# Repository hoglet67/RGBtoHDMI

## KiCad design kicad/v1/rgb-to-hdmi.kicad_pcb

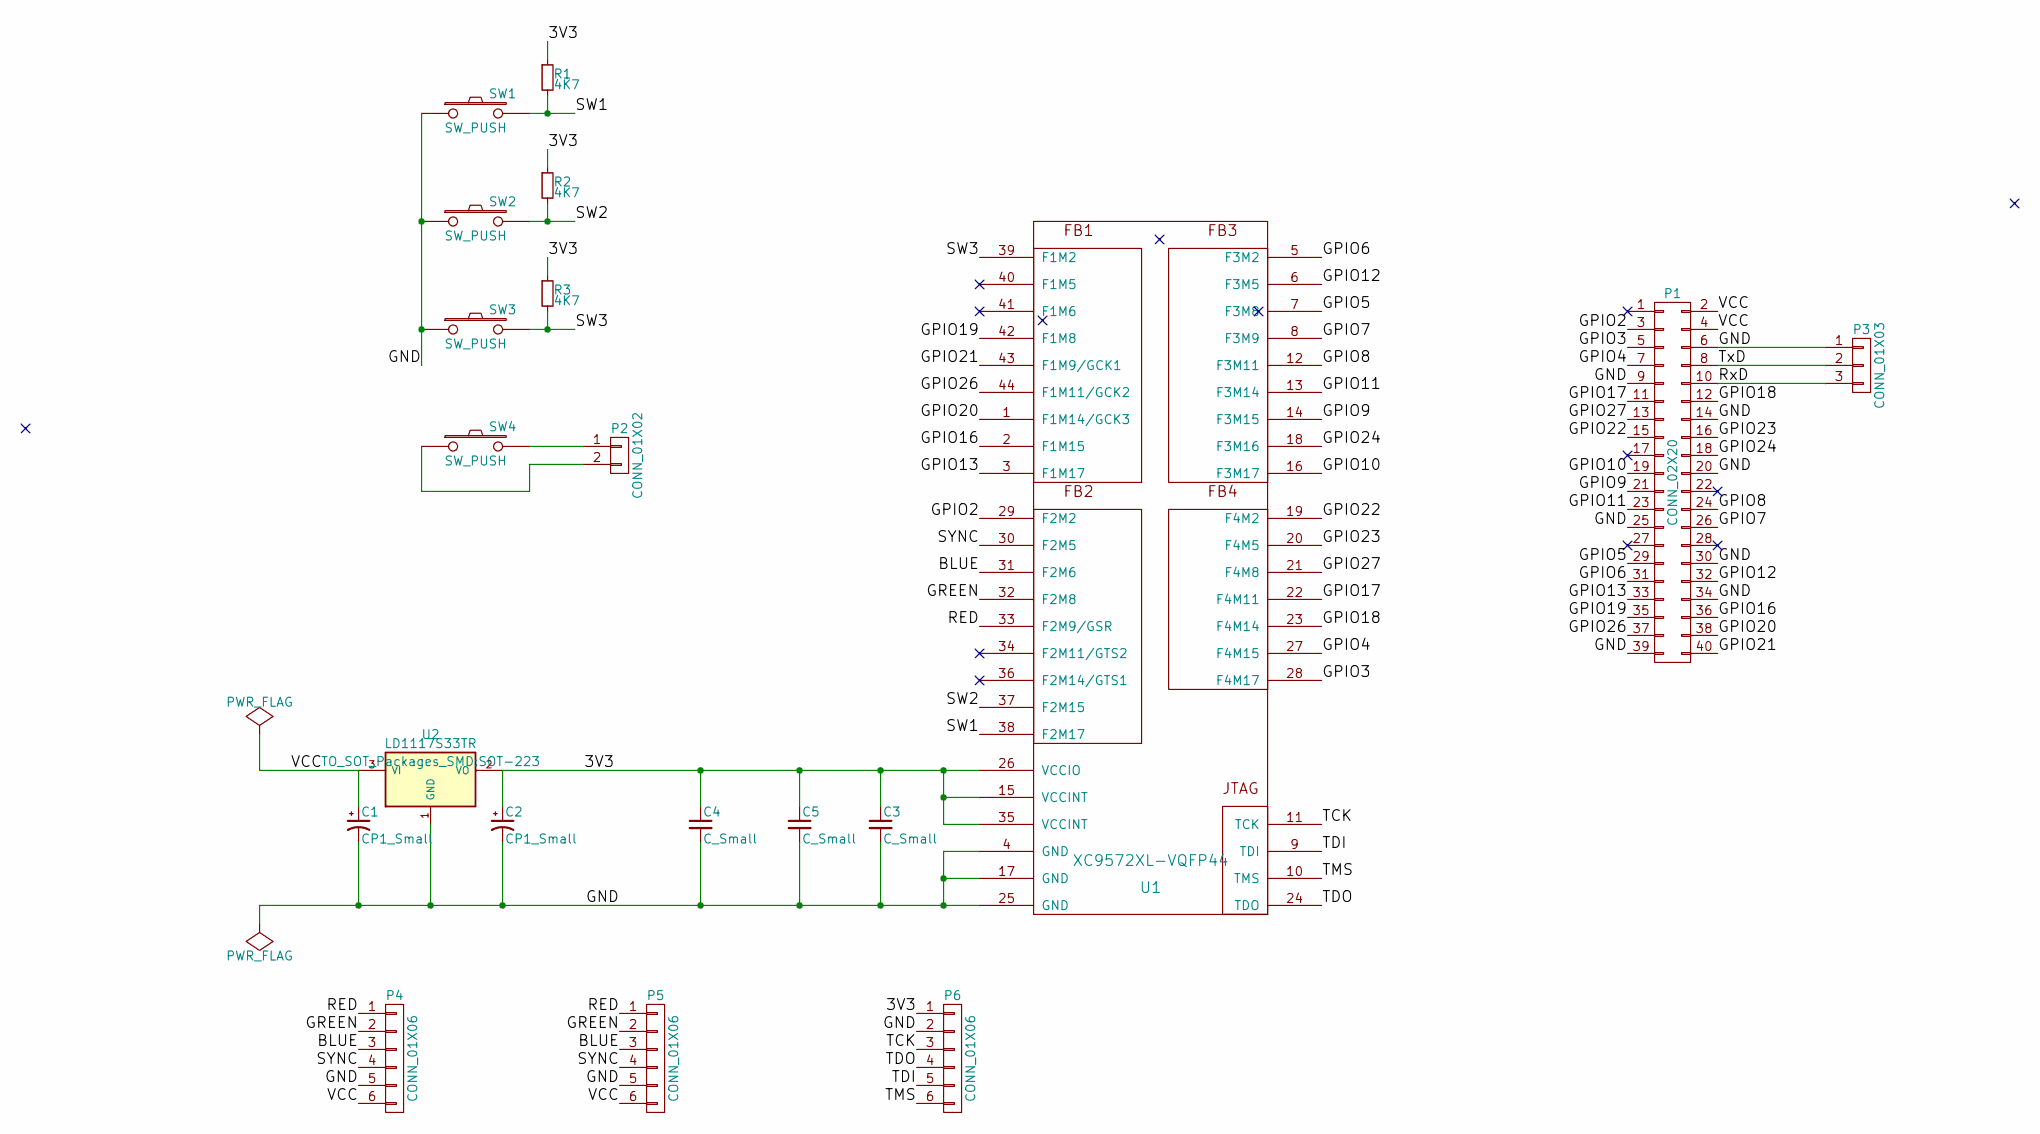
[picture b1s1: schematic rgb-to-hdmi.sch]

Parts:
C1, C2: CP1_Small; CP_Tantalum_Case-C_EIA-6032-28_Hand
C3, C4, C5: C_Small; C_Disc_D3.0mm_W1.6mm_P2.50mm
P1: CONN_02X20; Socket_Strip_Straight_2x20
P2: CONN_01X02; Pin_Header_Straight_1x02_Pitch2.54mm
P3: CONN_01X03; Pin_Header_Straight_1x03_Pitch2.54mm
P4: CONN_01X06; DIN45322
P5, P6: CONN_01X06; Pin_Header_Straight_1x06_Pitch2.54mm
R1, R2, R3: 4K7; R_Axial_DIN0207_L6.3mm_D2.5mm_P10.16mm_Horizontal
SW1, SW2, SW3, SW4: SW_PUSH; SW_PUSH_6mm_h5mm
U1: XC9572XL-VQFP44; LQFP-44_10x10mm_Pitch0.8mm
U2: LD1117S33TR; SOT-223

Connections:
/3V3: C2.1, C3.1, C4.1, C5.1, P6.1, R1.1, R2.1, R3.1, U1.15 (VCCINT), U1.26 (VCCIO), U1.35 (VCCINT), U2.2 (VO)
/BLUE: P4.3, P5.3, U1.31 (F2M6)
/GND: C1.2, C2.2, C3.2, C4.2, C5.2, P1.6, P1.9, P1.14, P1.20, P1.25, P1.30, P1.34, P1.39, P3.1, P4.5, P5.5, P6.2, SW1.1, SW2.1, SW3.1, U1.4 (GND), U1.17 (GND), U1.25 (GND), U2.1 (GND)
/GPIO2: P1.3, U1.29 (F2M2)
/GPIO3: P1.5, U1.28 (F4M17)
/GPIO4: P1.7, U1.27 (F4M15)
/GPIO5: P1.29, U1.7 (F3M8)
/GPIO6: P1.31, U1.5 (F3M2)
/GPIO7: P1.26, U1.8 (F3M9)
/GPIO8: P1.24, U1.12 (F3M11)
/GPIO9: P1.21, U1.14 (F3M15)
/GPIO10: P1.19, U1.16 (F3M17)
/GPIO11: P1.23, U1.13 (F3M14)
/GPIO12: P1.32, U1.6 (F3M5)
/GPIO13: P1.33, U1.3 (F1M17)
/GPIO16: P1.36, U1.2 (F1M15)
/GPIO17: P1.11, U1.22 (F4M11)
/GPIO18: P1.12, U1.23 (F4M14)
/GPIO19: P1.35, U1.42 (F1M8)
/GPIO20: P1.38, U1.1 (F1M14/GCK3)
/GPIO21: P1.40, U1.43 (F1M9/GCK1)
/GPIO22: P1.15, U1.19 (F4M2)
/GPIO23: P1.16, U1.20 (F4M5)
/GPIO24: P1.18, U1.18 (F3M16)
/GPIO26: P1.37, U1.44 (F1M11/GCK2)
/GPIO27: P1.13, U1.21 (F4M8)
/GREEN: P4.2, P5.2, U1.32 (F2M8)
/RED: P4.1, P5.1, U1.33 (F2M9/GSR)
/RxD: P1.10, P3.3
/SW1: R1.2, SW1.2, U1.38 (F2M17)
/SW2: R2.2, SW2.2, U1.37 (F2M15)
/SW3: R3.2, SW3.2, U1.39 (F1M2)
/SYNC: P4.4, P5.4, U1.30 (F2M5)
/TCK: P6.3, U1.11 (TCK)
/TDI: P6.5, U1.9 (TDI)
/TDO: P6.4, U1.24 (TDO)
/TMS: P6.6, U1.10 (TMS)
/TxD: P1.8, P3.2
/VCC: C1.1, P1.2, P1.4, P4.6, P5.6, U2.3 (VI)
unnamed: P2.1, SW4.2
unnamed: P2.2, SW4.1

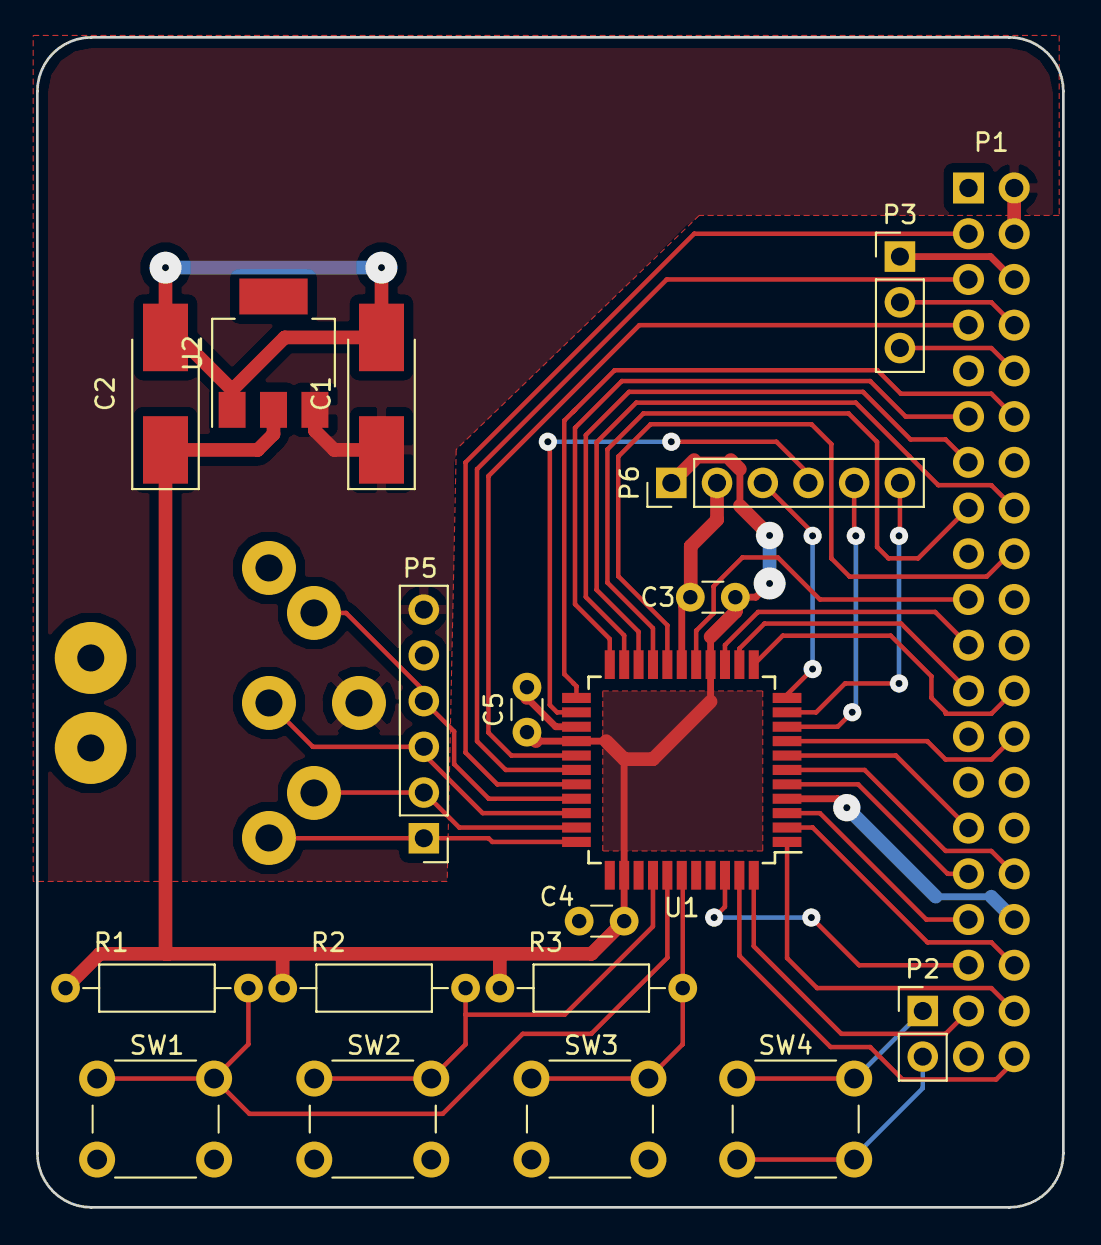
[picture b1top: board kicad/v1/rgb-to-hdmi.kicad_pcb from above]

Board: 2 copper layers, 57.0 x 65.0 mm, 20 parts (0 on the bottom side), 41 nets.

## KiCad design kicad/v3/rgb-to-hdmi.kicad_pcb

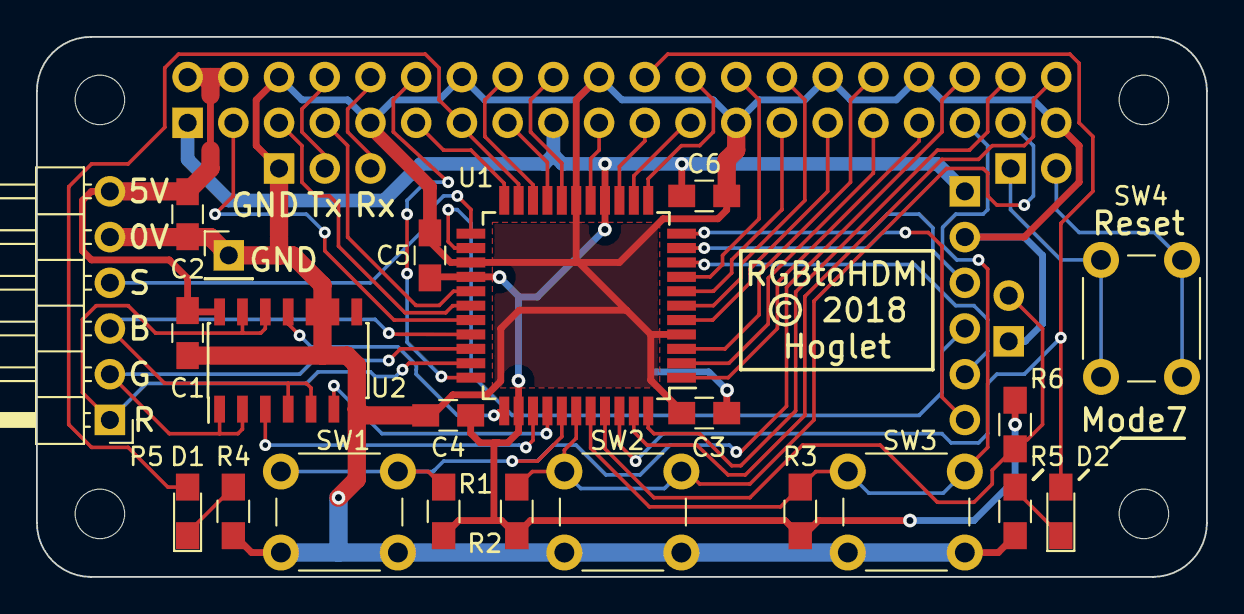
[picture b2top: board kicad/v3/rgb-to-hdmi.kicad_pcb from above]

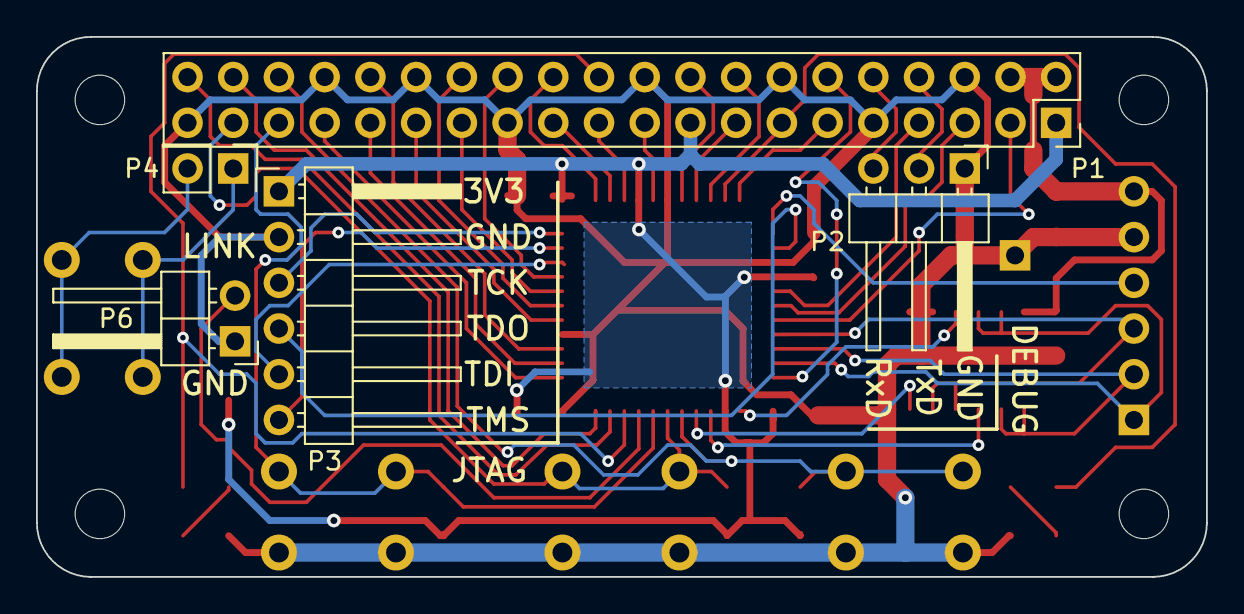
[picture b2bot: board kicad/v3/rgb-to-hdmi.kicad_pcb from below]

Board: 2 copper layers, 65.0 x 30.0 mm, 27 parts (5 on the bottom side), 47 nets.

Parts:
C1, C4, C5, C6: C_Small; C_0805_HandSoldering
C2, C3: CP1_Small; C_0805_HandSoldering
D1, D2: LED; LED_0805_HandSoldering
P1: CONN_02X20; Socket_Strip_Straight_2x20_Pitch2.54mm
P2: CONN_01X03; Pin_Header_Angled_1x03_Pitch2.54mm
P3, P5: CONN_01X06; Pin_Header_Angled_1x06_Pitch2.54mm
P4: CONN_01X02; Socket_Strip_Straight_1x02_Pitch2.54mm
P6: CONN_01X02; Pin_Header_Angled_1x02_Pitch2.54mm
P7: Conn_01x01; Pin_Header_Straight_1x01_Pitch2.54mm
R1, R2, R3: 4K7; R_0805_HandSoldering
R4, R5: 220R; R_0805_HandSoldering
R6: 10K; R_0805_HandSoldering
SW1, SW2, SW3, SW4: SW_PUSH; SW_PUSH_6mm_h5mm
U1: XC9572XL-VQFP44; LQFP-44_10x10mm_Pitch0.8mm
U2: 74LS08; SOIC-14_3.9x8.7mm_Pitch1.27mm

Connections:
/3V3: C3.1, C4.1, C5.1, C6.1, P1.1, P1.17, P3.1, R1.1, R2.1, R3.1, R6.1, U1.15, U1.26, U1.35
/BBLUE: U1.37, U2.6
/BGREEN: U1.36, U2.3
/BLUE: P5.3, U1.30, U2.4, U2.5
/BRED: U1.34, U2.11
/GPIO0: P1.27, U1.7
/GPIO1: P1.28, U1.6
/GPIO2: P1.3, U1.29
/GPIO3: P1.5, U1.28
/GPIO4: P1.7, U1.27
/GPIO5: P1.29, U1.5
/GPIO6: P1.31, U1.2
/GPIO7: P1.26, U1.8
/GPIO8: P1.24, U1.12
/GPIO9: P1.21, U1.14
/GPIO10: P1.19, U1.16
/GPIO11: P1.23, U1.13
/GPIO12: P1.32, U1.3
/GPIO13: P1.33, U1.1
/GPIO16: P1.36, R1.2, SW1.2, U1.38
/GPIO17: P1.11, U1.22
/GPIO18: P1.12, U1.33
/GPIO19: P1.35, R3.2, SW3.2, U1.40
/GPIO20: P1.38, U1.44
/GPIO21: P1.40, U1.43
/GPIO22: P1.15, U1.19
/GPIO23: P1.16, U1.20
/GPIO24: P1.18, U1.18
/GPIO25: D2.2, P1.22, U1.42
/GPIO26: P1.37, R2.2, SW2.2, U1.39
/GPIO27: D1.2, P1.13, U1.21
/GREEN: P5.2, U1.31, U2.1, U2.2
/LINK: P6.2, R6.2, U1.41
/RED: P5.1, U1.32, U2.12, U2.13
/RxD: P1.10, P2.3
/SYNC: P5.4, U1.23
/TCK: P3.3, U1.11
/TDI: P3.5, U1.9
/TDO: P3.4, U1.24
/TMS: P3.6, U1.10
/TxD: P1.8, P2.2
GND: C1.2, C2.2, C3.2, C4.2, C5.2, C6.2, P1.6, P1.9, P1.14, P1.20, P1.25, P1.30, P1.34, P1.39, P2.1, P3.2, P5.5, P6.1, P7.1, R4.2, R5.2, SW1.1, SW2.1, SW3.1, U1.4, U1.17, U1.25, U2.7, U2.9, U2.10
unnamed: D1.1, R4.1
unnamed: D2.1, R5.1
unnamed: P4.1, SW4.2
unnamed: P4.2, SW4.1
VCC: C1.1, C2.1, P1.2, P1.4, P5.6, U2.14

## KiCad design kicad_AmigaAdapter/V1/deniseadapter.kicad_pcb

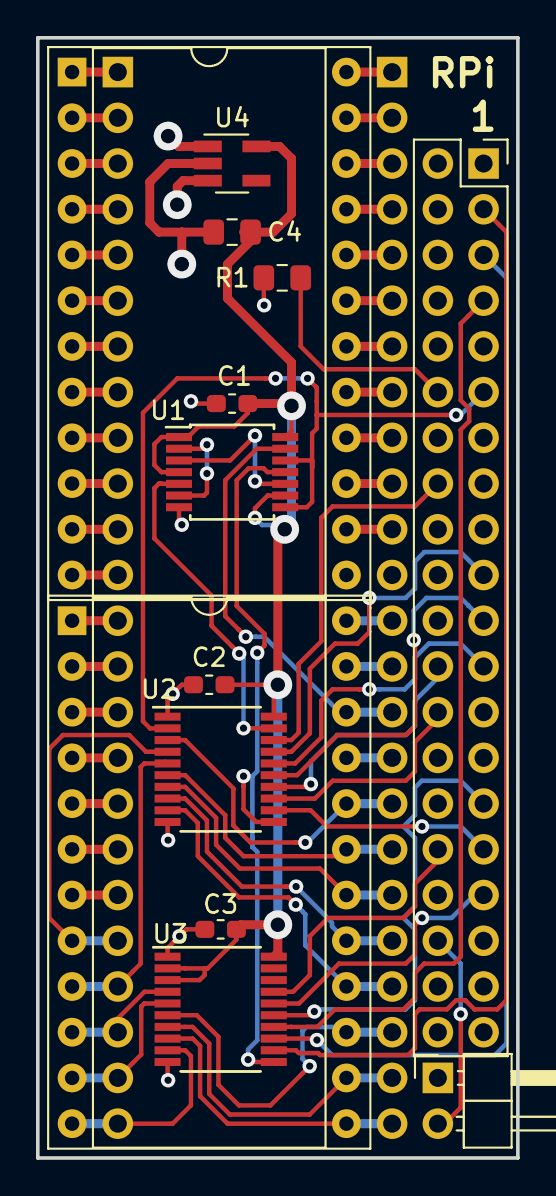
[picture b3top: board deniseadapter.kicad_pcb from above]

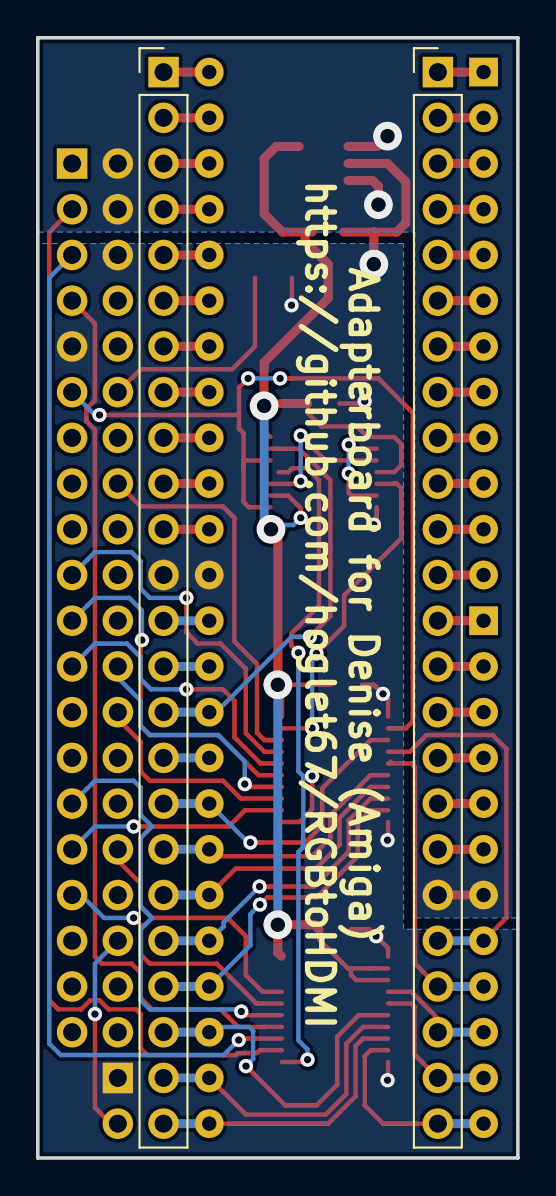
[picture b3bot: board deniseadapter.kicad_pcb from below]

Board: 2 copper layers, 26.7 x 62.2 mm, 15 parts (2 on the bottom side), 69 nets.

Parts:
C1, C2, C3: 100nF; C_0603_1608Metric_Pad1.05x0.95mm_HandSolder
C4: 1uF; C_0805_2012Metric_Pad1.15x1.40mm_HandSolder
JButton1: Conn_01x02; PinHeader_1x02_P2.54mm_Horizontal
JDenise1, JDenise2: Conn_02x12_Counter_Clockwise; DIP-24_W15.24mm_Socket
JMainBoard1, JMainBoard2: Conn_01x24; PinHeader_1x24_P2.54mm_Vertical
JRaspberryPiZero1: Conn_02x20_Odd_Even; PinSocket_2x20_P2.54mm_Vertical
R1: 3k3; R_0805_2012Metric_Pad1.15x1.40mm_HandSolder
U1: 74LVC86; TSSOP-14_4.4x5mm_P0.65mm
U2, U3: 74LVC574; TSSOP-20_4.4x6.5mm_P0.65mm
U4: TLV74333PDBVR; SOT-23-5_HandSoldering

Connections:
+3V3: C1.1, C2.1, C3.1, C4.1, U1.1, U1.4, U1.9, U1.14, U2.20, U3.2, U3.3, U3.20, U4.5
+5V: JDenise2.7, JMainBoard1.19, JRaspberryPiZero1.2, JRaspberryPiZero1.4, U4.1, U4.3
/B0: JDenise2.12, JMainBoard1.24, U3.9
/B1: JDenise2.13, JMainBoard2.24, U3.8
/B2: JDenise2.14, JMainBoard2.23, U3.7
/B3: JDenise2.15, JMainBoard2.22, U3.6
/CDAC: JDenise2.22, JMainBoard2.15, U1.13
/CSYNC: JDenise2.20, JMainBoard2.17, U2.3
/G0: JDenise2.16, JMainBoard2.21, U2.9
/G1: JDenise2.17, JMainBoard2.20, U2.8
/G2: JDenise2.18, JMainBoard2.19, U2.7
/G3: JDenise2.19, JMainBoard2.18, U2.6
/PiB0: JRaspberryPiZero1.3, U3.12
/PiB1: JRaspberryPiZero1.5, U3.13
/PiB2: JRaspberryPiZero1.7, U3.14
/PiB3: JRaspberryPiZero1.29, U3.15
/PiCLK: JRaspberryPiZero1.11, U1.8, U1.12, U2.2
/PiCSYNC: JRaspberryPiZero1.16, U2.18
/PiG0: JRaspberryPiZero1.31, U2.12
/PiG1: JRaspberryPiZero1.26, U2.13
/PiG2: JRaspberryPiZero1.24, U2.14
/PiG3: JRaspberryPiZero1.21, U2.15
/PiR0: JRaspberryPiZero1.19, U2.17
/PiR1: JRaspberryPiZero1.23, U2.16
/PiR2: JRaspberryPiZero1.32, U3.17
/PiR3: JRaspberryPiZero1.33, U3.16
/R0: JDenise2.8, JMainBoard1.20, U2.4
/R1: JDenise2.9, JMainBoard1.21, U2.5
/R2: JDenise2.10, JMainBoard1.22, U3.4
/R3: JDenise2.11, JMainBoard1.23, U3.5
GND: C1.2, C2.2, C3.2, C4.2, JButton1.1, JDenise1.13, JMainBoard2.12, JRaspberryPiZero1.6, JRaspberryPiZero1.9, R1.2, U1.7, U2.1, U2.10, U3.1, U3.10, U4.2
unnamed: JButton1.2, JRaspberryPiZero1.36
unnamed: JDenise1.1, JMainBoard1.1
unnamed: JDenise1.2, JMainBoard1.2
unnamed: JDenise1.3, JMainBoard1.3
unnamed: JDenise1.4, JMainBoard1.4
unnamed: JDenise1.5, JMainBoard1.5
unnamed: JDenise1.6, JMainBoard1.6
unnamed: JDenise1.7, JMainBoard1.7
unnamed: JDenise1.8, JMainBoard1.8
unnamed: JDenise1.9, JMainBoard1.9
unnamed: JDenise1.10, JMainBoard1.10
unnamed: JDenise1.11, JMainBoard1.11
unnamed: JDenise1.12, JMainBoard1.12
unnamed: JDenise1.14, JMainBoard2.11
unnamed: JDenise1.15, JMainBoard2.10
unnamed: JDenise1.16, JMainBoard2.9
unnamed: JDenise1.17, JMainBoard2.8
unnamed: JDenise1.18, JMainBoard2.7
unnamed: JDenise1.19, JMainBoard2.6
unnamed: JDenise1.20, JMainBoard2.5
unnamed: JDenise1.21, JMainBoard2.4
unnamed: JDenise1.22, JMainBoard2.3
unnamed: JDenise1.23, JMainBoard2.2
unnamed: JDenise1.24, JMainBoard2.1
unnamed: JDenise2.1, JMainBoard1.13
unnamed: JDenise2.2, JMainBoard1.14
unnamed: JDenise2.3, JMainBoard1.15
unnamed: JDenise2.4, JMainBoard1.16
unnamed: JDenise2.5, JMainBoard1.17
unnamed: JDenise2.6, JMainBoard1.18
unnamed: JDenise2.21, JMainBoard2.16
unnamed: JDenise2.23, JMainBoard2.14
unnamed: JDenise2.24, JMainBoard2.13
unnamed: JRaspberryPiZero1.12, R1.1
unnamed: U1.2, U1.6
unnamed: U1.5, U2.19
unnamed: U1.3, U1.10
unnamed: U1.11, U2.11, U3.11

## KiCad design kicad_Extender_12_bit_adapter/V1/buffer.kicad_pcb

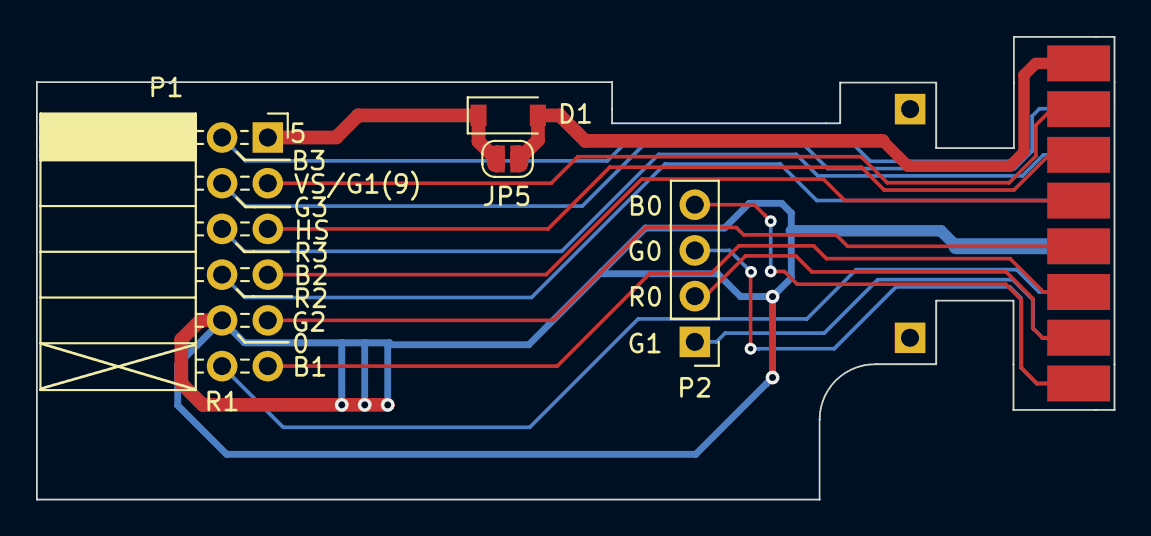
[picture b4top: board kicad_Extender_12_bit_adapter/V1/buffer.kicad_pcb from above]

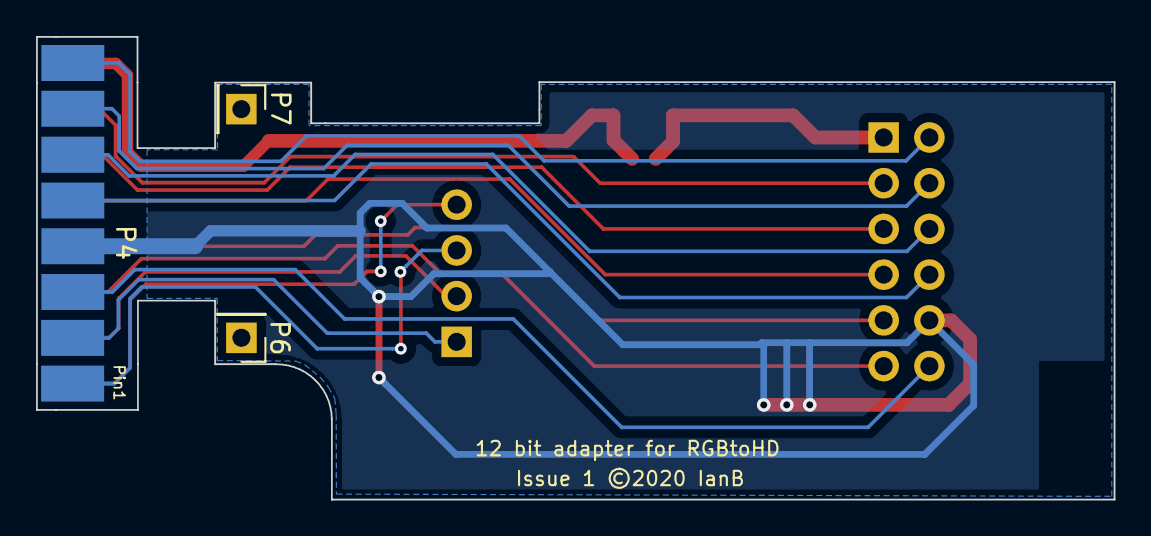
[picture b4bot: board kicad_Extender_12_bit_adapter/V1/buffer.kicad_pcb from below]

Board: 2 copper layers, 59.9 x 25.7 mm, 8 parts (3 on the bottom side), 17 nets.

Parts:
D1: D_Schottky; D_SOD-123
JP5: SolderJumper_2_Open; SolderJumper-2_P1.3mm_Open_RoundedPad1.0x1.5mm
P1: Conn_02x06_Odd_Even; PinSocket_2x06_P2.54mm_Horizontal
P2: Conn_01x04; PinHeader_1x04_P2.54mm_Vertical
P4: Conn_01x08_odd; Harwin_M20-89006xx_1x08_P2.54mm_Horizontal_ODD
P5: Conn_01x08_even; Harwin_M20-89006xx_1x08_P2.54mm_Horizontal_EVEN
P6, P7: Conn_01x01; PinHeader_1x01_P2.54mm_Vertical

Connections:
/B0: P2.4, P5.2
/B1: P1.11, P5.6
/B2: P1.7, P5.10
/B3: P1.2, P4.15
/G0: P2.3, P4.1
/G1: P2.1, P4.3
/G2: P1.9, P5.8
/G3: P1.4, P4.13
/GND: P1.10, P4.7
/R0: P2.2, P5.4
/R1: P1.12, P4.5
/R2: P1.8, P4.9
/R3: P1.6, P4.11
/SYNC: P1.5, P5.12
/VCC: D1.1, JP5.2, P1.1
/VCC_IN: D1.2, JP5.1, P5.16
/VSYNC: P1.3, P5.14

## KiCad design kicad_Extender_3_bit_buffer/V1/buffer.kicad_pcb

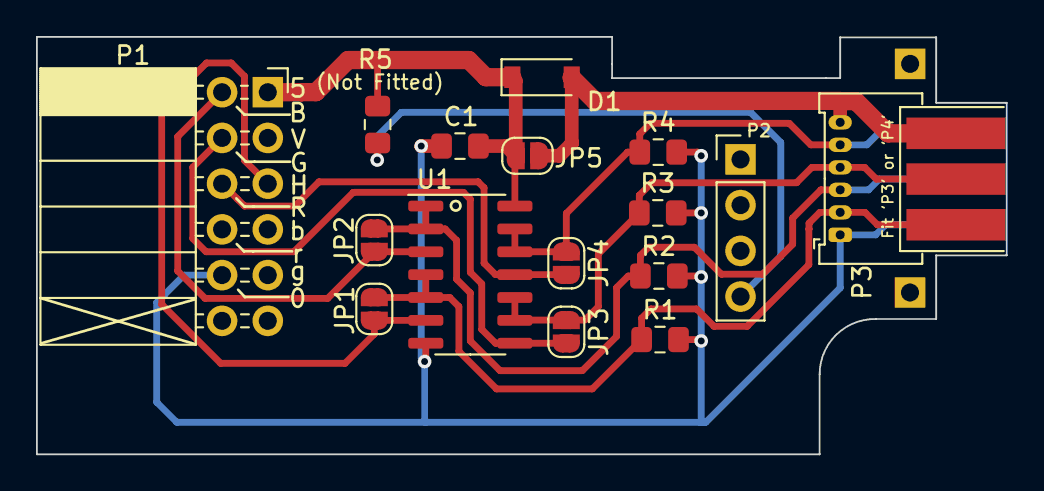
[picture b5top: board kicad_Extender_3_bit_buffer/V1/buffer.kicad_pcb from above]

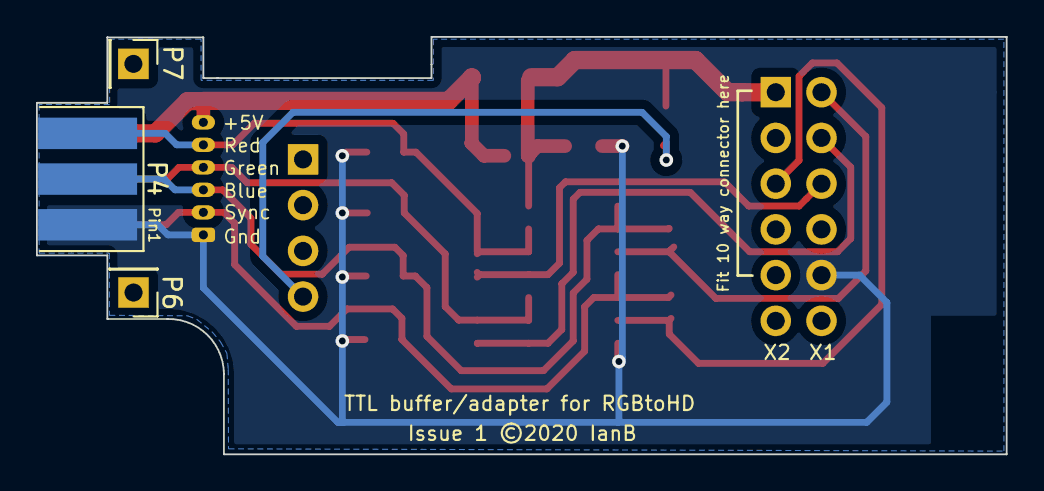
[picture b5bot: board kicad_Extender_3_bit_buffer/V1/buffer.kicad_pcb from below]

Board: 2 copper layers, 53.9 x 23.2 mm, 20 parts (3 on the bottom side), 12 nets.

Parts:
C1: 100n; C_0805_2012Metric_Pad1.15x1.40mm_HandSolder
D1: D_Schottky; D_SOD-123
JP1, JP2, JP3, JP4, JP5: SolderJumper_2_Open; SolderJumper-2_P1.3mm_Open_RoundedPad1.0x1.5mm
P1: Conn_02x06_Odd_Even; PinSocket_2x06_P2.54mm_Horizontal
P2: Conn_01x04; PinHeader_1x04_P2.54mm_Vertical
P3: Conn_01x06; Molex_PicoBlade_53048-0610_1x06_P1.25mm_Horizontal_Custom2
P4: Conn_01x03_ODD; Harwin_M20-89003xx_1x03_P2.54mm_Horizontal_Custom_ODD2
P5: Conn_01x03_EVEN; Harwin_M20-89003xx_1x03_P2.54mm_Horizontal_Custom_EVEN2
P6, P7: Conn_01x01; PinHeader_1x01_P2.54mm_Vertical
R1, R2, R3, R4: 47K; R_0805_2012Metric_Pad1.15x1.40mm_HandSolder
R5: 1K; R_0805_2012Metric_Pad1.15x1.40mm_HandSolder
U1: 74LS08; SOIC-14_3.9x8.7mm_P1.27mm

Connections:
/ABLUE: JP2.1, P3.3, P4.3, R2.1, U1.1, U1.2
/AGREEN: JP3.1, P3.4, P5.4, R3.1, U1.9, U1.10
/ARED: JP4.1, P3.5, P4.5, R4.1, U1.12, U1.13
/ASYNC: JP1.1, P3.2, P5.2, R1.1, U1.4, U1.5
/BLUE: JP2.2, P1.2, U1.3
/GND: C1.2, P1.10, P3.1, P4.1, R1.2, R2.2, R3.2, R4.2, U1.7
/GREEN: JP3.2, P1.4, U1.8
/RED: JP4.2, P1.6, U1.11
/SYNC: JP1.2, P1.5, U1.6
/VCC: C1.1, D1.1, JP5.2, P1.1, R5.1, U1.14
/VCC_IN: D1.2, JP5.1, P3.6, P5.6
unnamed: P2.4, R5.2

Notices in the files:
kicad/v3/rgb-to-hdmi.kicad_pcb:
© 2018
kicad_Extender_12_bit_adapter/V1/buffer.kicad_pcb:
Issue 1 ©2020 IanB
